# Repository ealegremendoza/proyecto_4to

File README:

Este repositorio contiene gran parte del proyecto de cuarto año a de la carrera de Ingeniería Electrónica de la UTN-FRBA.

Breve descripción de las carptas 
---------------------------------------------------------------------------------------------
En la carpeta "docs" se encuentra toda documentación relacionada al proyecto.
En la carpeta "csv" se encuentran los archivos *.csv para la aplicación.

En la carpeta "code" se encuentra todo código relacionado al proyecto.
En la carpeta "code/dsp" se encuentran las clases para el procesamiento de señales.
En la carpeta "code/gui" se encuentran las clases relacionadas a la interfaz gráfica de la aplicación.

En la carpeta "pcb" se encuentra todos los archivos KiCad relacionados al diseño del PCB.

En la carpeta "lpc_info" se encontrará información útil sobre el microcontrolador utilizado.

NOTAS IMPORTANTES
---------------------------------------------------------------------------------------------

- La interfaz gráfica de este proyecto es realizada en código Python 3.6.5., bajo la plataforma ANACONDA3.
- Hoy en día el código funciona en un SO Ubuntu 16.04 LTS.
- Para correr la aplicación:

	Desde la terminal en el directorio code:
		python3 app.py 

	O desde la terminal en el directorio proyecto_4to:
		python3 code/app.py

	Desde SPYDER:
		Abrir el archivo app.py que se encuentra en el directorio code.
		Presionar F5.
---------------------------------------------------------------------------------------------

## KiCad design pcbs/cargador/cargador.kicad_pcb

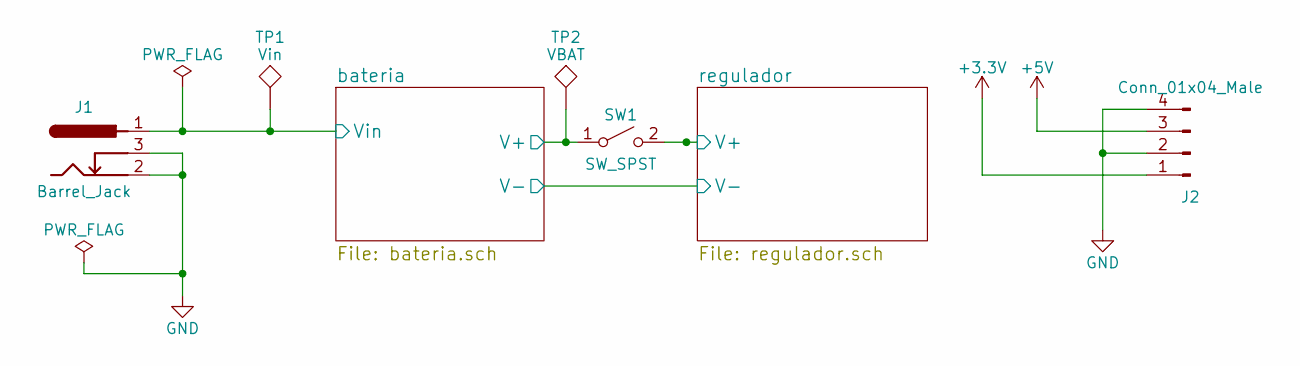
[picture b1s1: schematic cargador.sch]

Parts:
J1: Barrel_Jack; BARREL_JACK
J2: Conn_01x04_Male; Pin_Header_Straight_1x04_Pitch2.54mm
SW1: SW_SPST; Pin_Header_Straight_1x02_Pitch2.54mm
TP1: Vin; TestPoint_Plated_Hole_D2.0mm
TP2: VBAT; TestPoint_Plated_Hole_D2.0mm

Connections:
+3V3: J2.1; also elsewhere on the board
+5V: J2.3; also elsewhere on the board
/bateria/V+: SW1.1 (A), TP2.1; also elsewhere on the board
/regulador/V+: SW1.2 (B); also elsewhere on the board
GND: J1.2, J1.3, J2.2, J2.4; also elsewhere on the board
VCC: J1.1, TP1.1; also elsewhere on the board

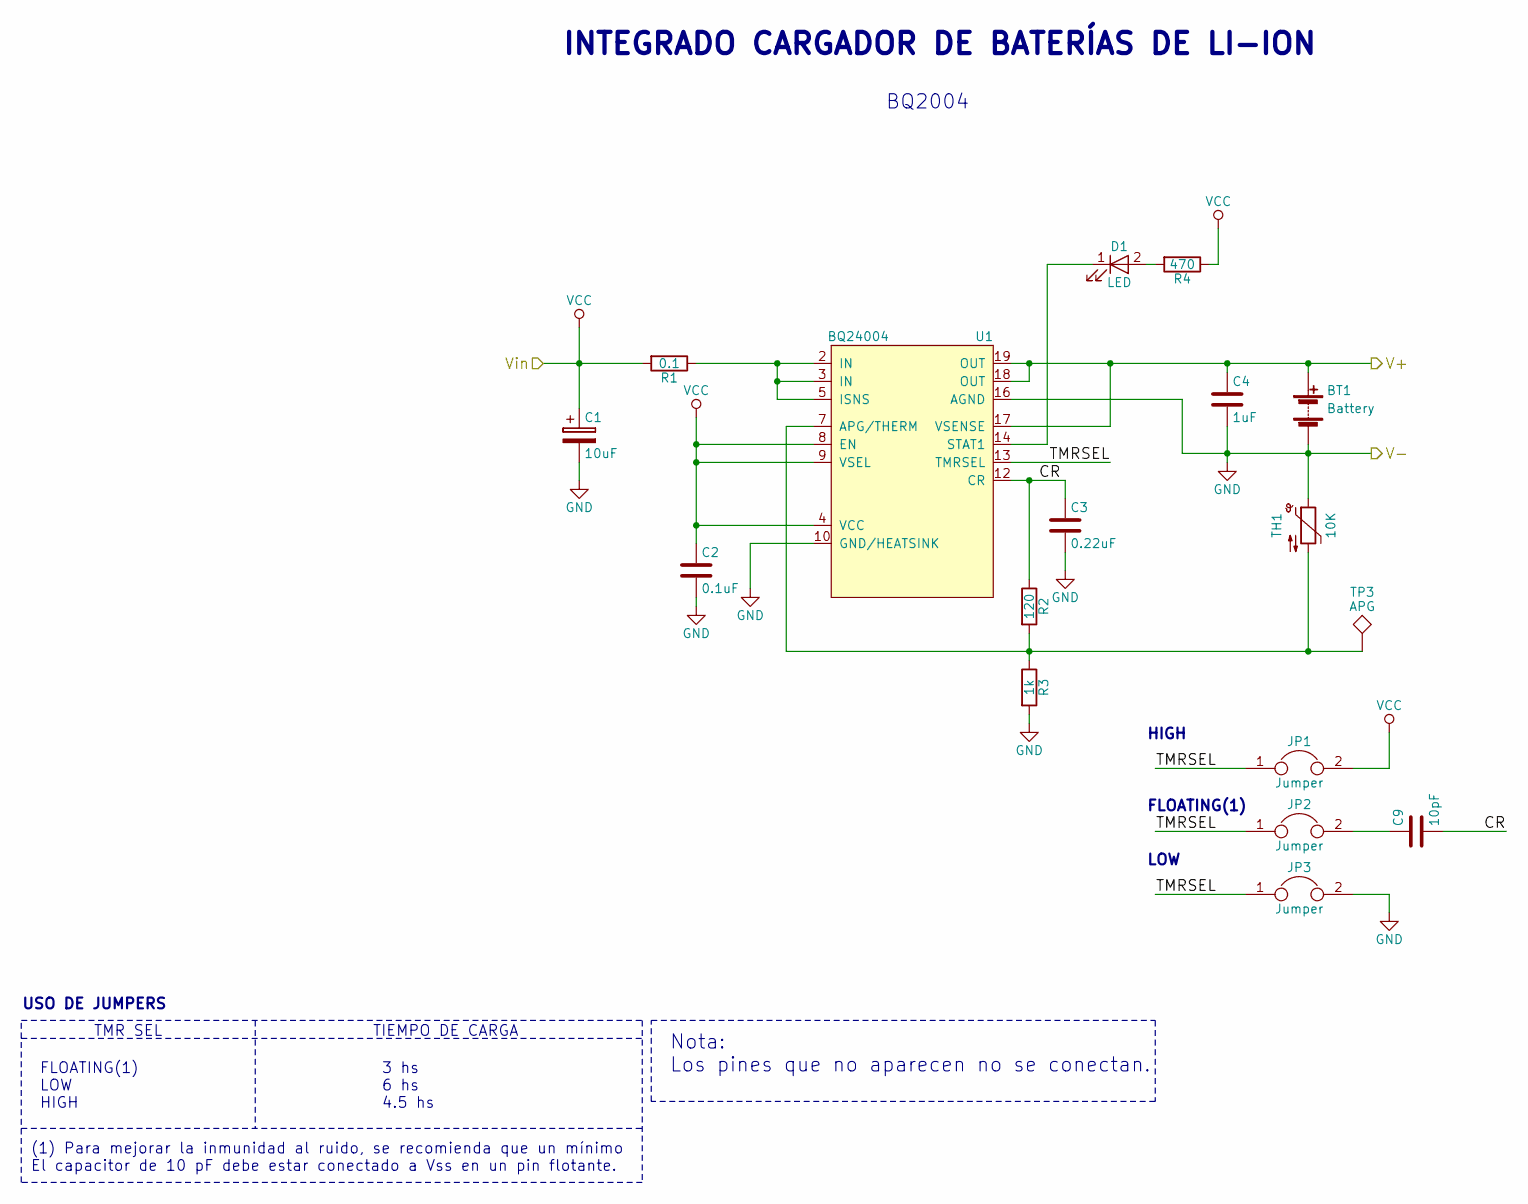
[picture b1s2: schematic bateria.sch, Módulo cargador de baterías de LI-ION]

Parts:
BT1: Battery; TerminalBlock_bornier-2_P5.08mm
C1: 10uF; CP_Tantalum_Case-A_EIA-3216-18_Hand
C2: 0.1uF; C_0805_HandSoldering
C3: 0.22uF; C_0805_HandSoldering
C4: 1uF; C_0805_HandSoldering
C9: 10pF; C_0805_HandSoldering
D1: LED; LED_1206_HandSoldering
JP1, JP2, JP3: Jumper; Pin_Header_Straight_1x02_Pitch2.54mm
R1: 0.1; R_2512_HandSoldering
R2: 120; R_0805_HandSoldering
R3: 1k; R_0805_HandSoldering
R4: 470; R_0805_HandSoldering
TH1: 10K; R_Axial_DIN0207_L6.3mm_D2.5mm_P2.54mm_Vertical
TP3: APG; TestPoint_Plated_Hole_D2.0mm
U1: BQ24004; HTSSOP-20-1EP_4.4x6.5mm_Pitch0.65mm_ThermalPad

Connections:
/bateria/CR: C3.1, C9.2, R2.1, U1.12 (CR)
/bateria/TMRSEL: JP1.1, JP2.1, JP3.1, U1.13 (TMRSEL)
/bateria/V+: BT1.1 (+), C4.1, U1.17 (VSENSE), U1.18 (OUT), U1.19 (OUT); also elsewhere on the board
GND: BT1.2 (-), C1.2, C2.2, C3.2, C4.2, JP3.2, R3.2, TH1.1, U1.10 (GND/HEATSINK), U1.16 (AGND); also elsewhere on the board
unnamed: C9.1, JP2.2
unnamed: D1.1 (K), U1.14 (STAT1)
unnamed: D1.2 (A), R4.2
unnamed: R1.1, U1.2 (IN), U1.3 (IN), U1.5 (ISNS)
unnamed 12: R2.2, R3.1, TH1.2, TP3.1, U1.7 (APG/THERM); also elsewhere on the board
VCC: C1.1, C2.1, JP1.2, R1.2, R4.1, U1.4 (VCC), U1.8 (EN), U1.9 (VSEL); also elsewhere on the board

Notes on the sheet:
INTEGRADO CARGADOR DE BATERÍAS DE LI-ION
BQ2004
Nota: Los pines que no aparecen no se conectan.
FLOATING(1) LOW HIGH
3 hs 6 hs 4.5 hs
TMR SEL
TIEMPO DE CARGA
(1) Para mejorar la inmunidad al ruido, se recomienda que un mínimo El capacitor de 10 pF debe estar conectado a Vss en un pin flotante.
USO DE JUMPERS
HIGH
FLOATING(1)
LOW

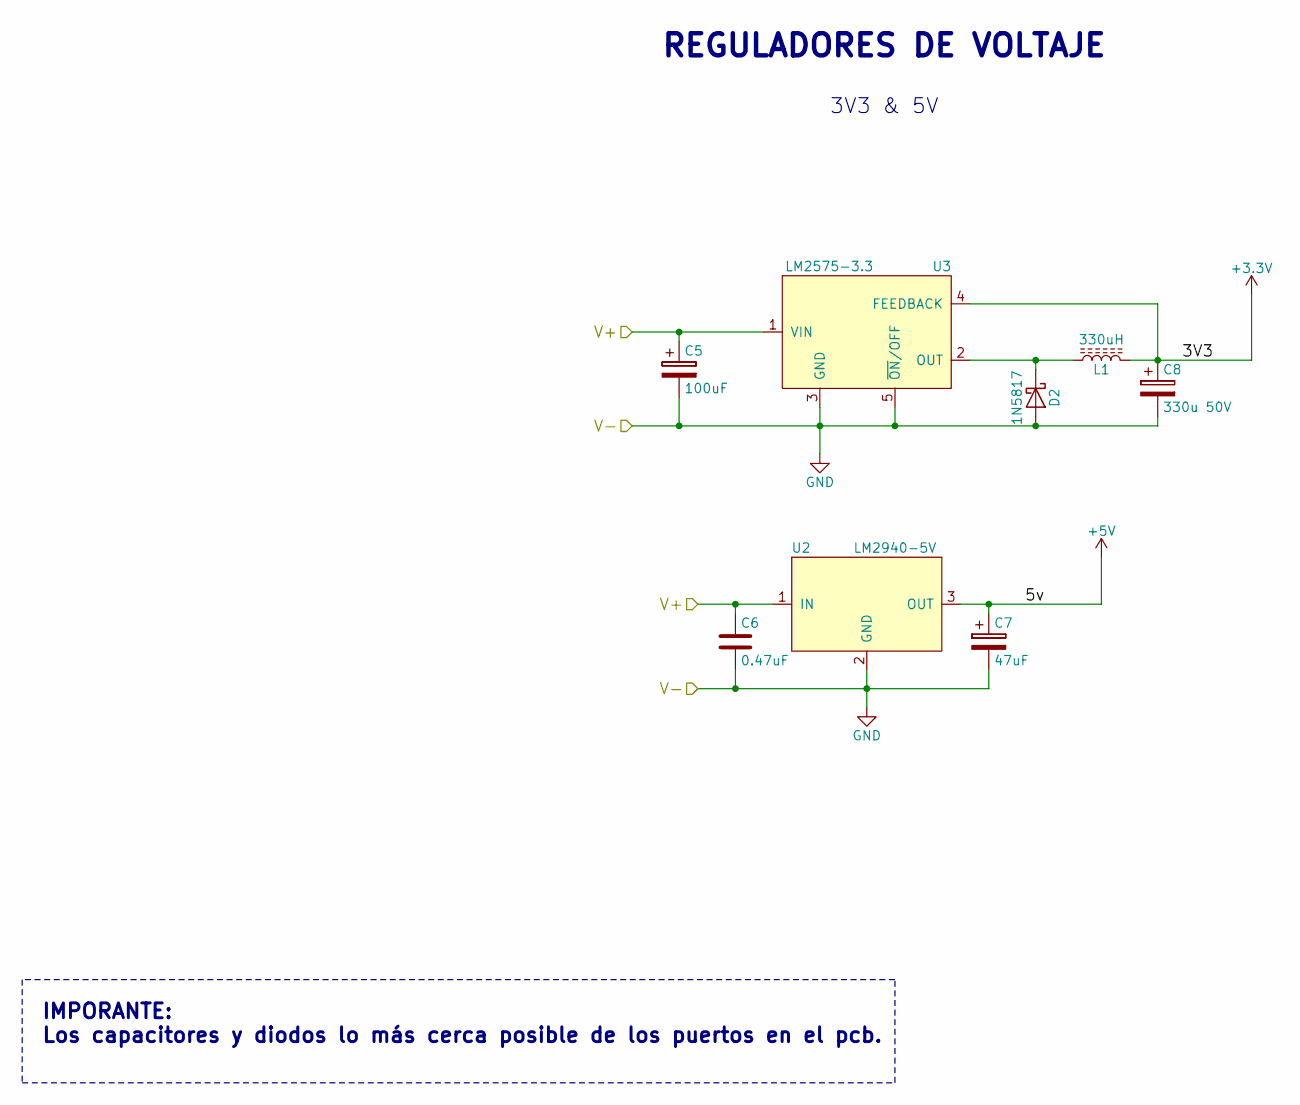
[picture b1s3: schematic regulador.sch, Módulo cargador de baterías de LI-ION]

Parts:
C5: 100uF; CP_Elec_6.3x5.3
C6: 0.47uF; CP_Tantalum_Case-A_EIA-3216-18_Hand
C7: 47uF; CP_Tantalum_Case-C_EIA-6032-28_Hand
C8: 330u 50V; CP_Elec_6.3x7.7
D2: 1N5817; D_DO-41_SOD81_P7.62mm_Horizontal
L1: 330uH; Choke_PK0810
U2: LM2940-5V; SOT-223-3_TabPin2
U3: LM2575-3.3; TO-263-5_TabPin3

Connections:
+3V3: C8.1, L1.2, U3.4 (FEEDBACK); also elsewhere on the board
+5V: C7.1, U2.3 (OUT); also elsewhere on the board
/regulador/V+: C5.1, C6.1, U2.1 (IN), U3.1 (VIN); also elsewhere on the board
GND: C5.2, C6.2, C7.2, C8.2, D2.2 (A), U2.2 (GND), U3.3 (GND), U3.5 (~ON~/OFF); also elsewhere on the board
unnamed: D2.1 (K), L1.1, U3.2 (OUT)

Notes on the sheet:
REGULADORES DE VOLTAJE
3V3 & 5V
IMPORANTE: Los capacitores y diodos lo más cerca posible de los puertos en el pcb.

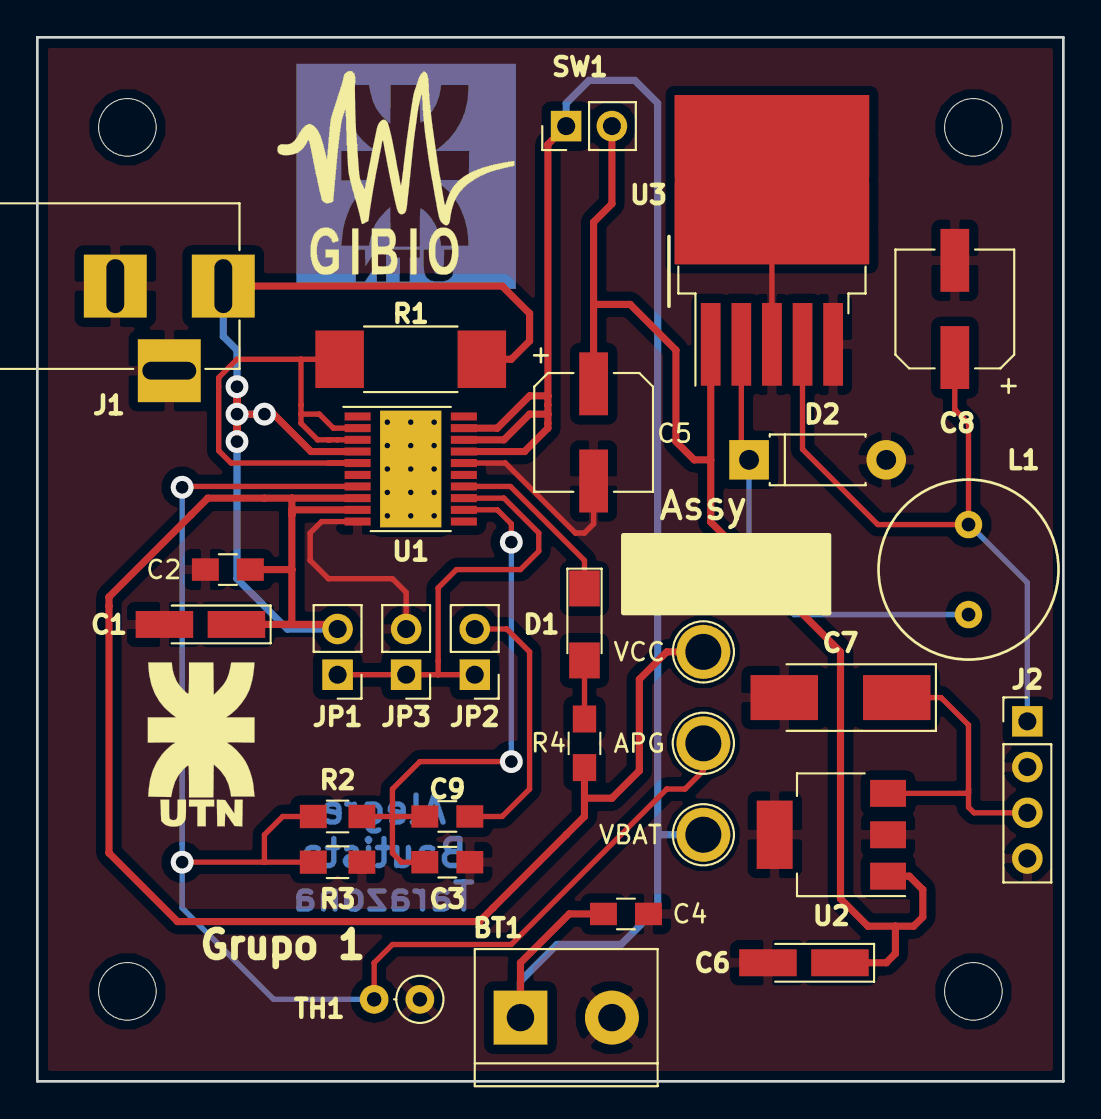
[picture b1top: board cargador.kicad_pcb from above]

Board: 2 copper layers, 57.0 x 58.0 mm, 38 parts (1 on the bottom side), 14 nets.

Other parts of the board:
 : logoUTN1
  : MountingHole_3.2mm_M3_DIN965
  #2: MountingHole_3.2mm_M3_DIN965
 #2,  #3: MountingHole_3.2mm_M3_DIN965
 #4: logoGIBIO
 #5: logoGIBIO5
 #6: logoUTN3
APG: APG; TestPoint_Plated_Hole_D2.0mm
VBAT: VBAT; TestPoint_Plated_Hole_D2.0mm
VCC: Vin; TestPoint_Plated_Hole_D2.0mm

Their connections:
/bateria/V+: VBAT.1; also elsewhere on the board
unnamed 12: APG.1; also elsewhere on the board
VCC: VCC.1; also elsewhere on the board

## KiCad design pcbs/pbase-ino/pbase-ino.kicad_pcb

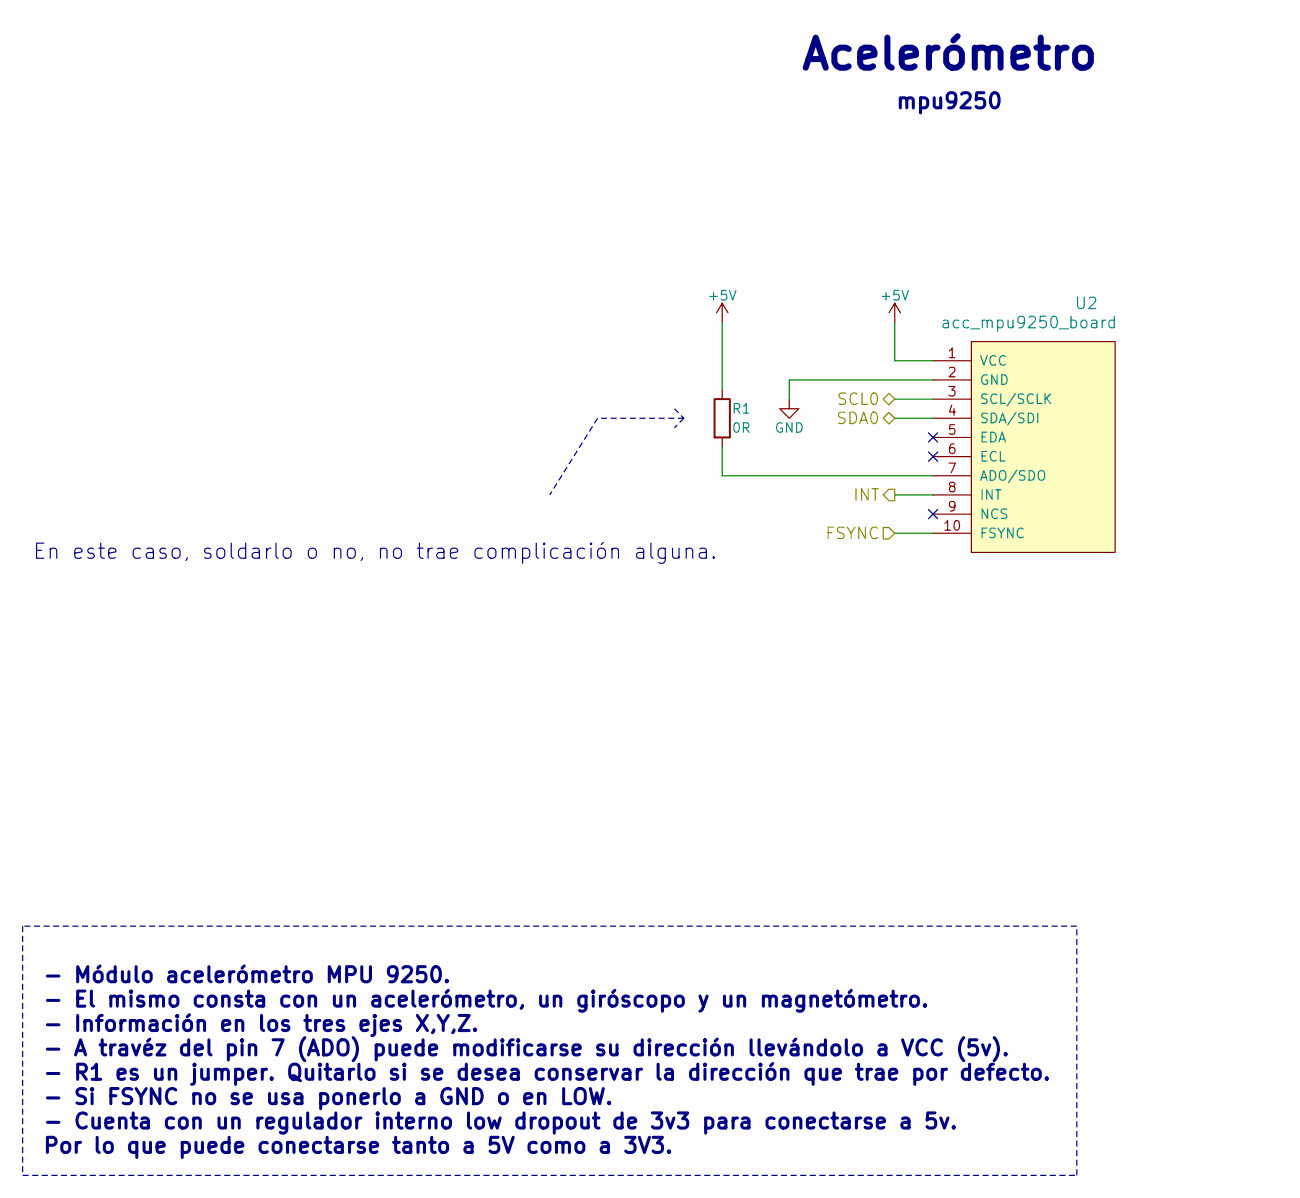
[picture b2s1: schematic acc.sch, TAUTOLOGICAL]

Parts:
R1: 0R; R_0805_HandSoldering
U2: acc_mpu9250_board; mpu9250_board

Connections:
+5V: R1.1, U2.1 (VCC); also elsewhere on the board
/Microcontrolador/FSYNC: U2.10 (FSYNC); also elsewhere on the board
/Microcontrolador/INT: U2.8 (INT); also elsewhere on the board
/Microcontrolador/SCL0: U2.3 (SCL/SCLK); also elsewhere on the board
/Microcontrolador/SDA0: U2.4 (SDA/SDI); also elsewhere on the board
GND: U2.2 (GND); also elsewhere on the board
unnamed: R1.2, U2.7 (ADO/SDO)

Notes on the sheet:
Acelerómetro
- Módulo acelerómetro MPU 9250. - El mismo consta con un acelerómetro, un giróscopo y un magnetómetro. - Información en los tres ejes X,Y,Z. - A travéz del pin 7 (ADO) puede modificarse su dirección llevándolo a VCC (5v). - R1 es un jumper. Quitarlo si se desea conservar la dirección que trae por d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
mpu9250
En este caso, soldarlo o no, no trae complicación alguna.

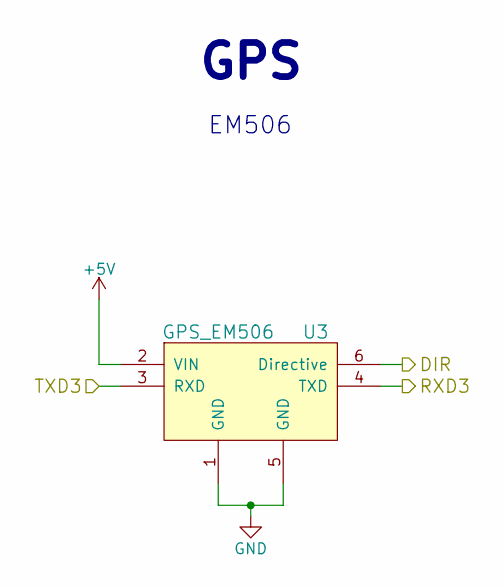
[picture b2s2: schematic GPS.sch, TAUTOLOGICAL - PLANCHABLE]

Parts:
U3: GPS_EM506; JST_SH_SM06B-SRSS-TB_06x1.00mm_Angled

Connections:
+5V: U3.2 (VIN); also elsewhere on the board
/GPS/DIR: U3.6 (Directive); also elsewhere on the board
/GPS/RXD3: U3.4 (TXD); also elsewhere on the board
/GPS/TXD3: U3.3 (RXD); also elsewhere on the board
GND: U3.1 (GND), U3.5 (GND); also elsewhere on the board

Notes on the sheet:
GPS
EM506

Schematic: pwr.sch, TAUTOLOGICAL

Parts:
C3: 100u; CP_Elec_6.3x5.3
C4: 330u; CP_Elec_10x10.5
D1: 1N5817; D_DO-41_SOD81_P7.62mm_Horizontal
J2: Screw_Terminal_01x02; TerminalBlock_bornier-2_P5.08mm
L1: L_Core_Ferrite; Choke_PK0810
SW1: SW_SPST; TerminalBlock_bornier-2_P5.08mm
TP21: VBAT; TestPoint_THTPad_D1.5mm_Drill0.7mm
TP22: 3V3; TestPoint_THTPad_D1.5mm_Drill0.7mm
U1: LM2575-3.3; TO-263-5_TabPin3

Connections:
+3V3: C4.1, D1.1 (K), L1.2, TP22.1, U1.2 (OUT); also elsewhere on the board
/Alimentación/VBat: C3.1, SW1.2, TP21.1, U1.1 (VIN); also elsewhere on the board
GND: C3.2, C4.2, D1.2 (A), J2.1, U1.3 (GND), U1.5 (~ON~/OFF); also elsewhere on the board
unnamed: J2.2, SW1.1
unnamed: L1.1, U1.4 (FEEDBACK)

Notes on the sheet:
Alimentación
IMPORTANTE: C3, D1 y C4 lo mas cerca posible del puerto y GND.
Fuente Switching 3v3
3V3: - Tarjeta SD - Comunicación Inalámbrica Zigbee. VBAT: - Arduino MEGA 5v: - GPS. EM506. - Acelerómetro. MPU9250.

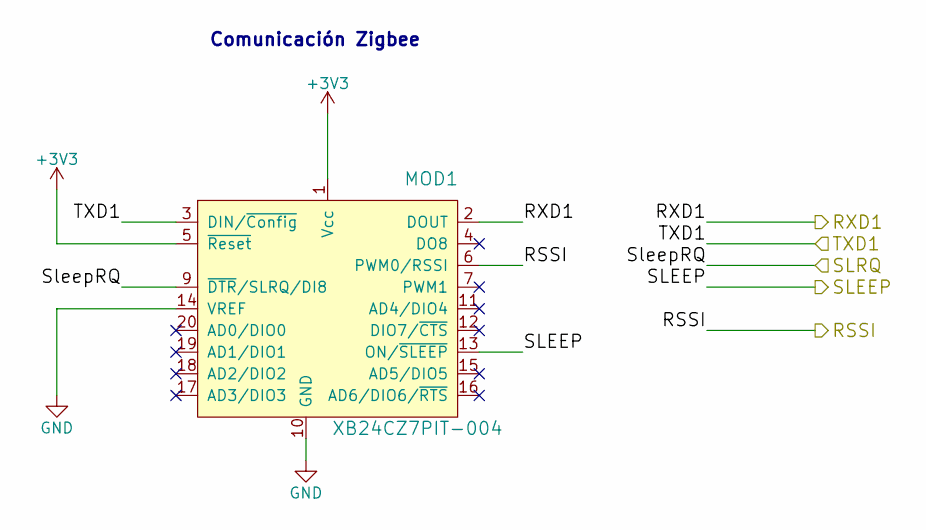
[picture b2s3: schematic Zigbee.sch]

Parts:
MOD1: XB24CZ7PIT-004; xbee_xb24cz7pit_004; MPN XB24CZ7PIT-004; Digi-Key_PN 602-1557-ND

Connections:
+3V3: MOD1.1 (Vcc), MOD1.5 (~Reset); also elsewhere on the board
/Microcontrolador/CAP2.1: MOD1.6 (PWM0/RSSI); also elsewhere on the board
/Microcontrolador/RXD1: MOD1.2 (DOUT); also elsewhere on the board
/Microcontrolador/SLEEP: MOD1.13 (ON/~SLEEP); also elsewhere on the board
/Microcontrolador/TXD1: MOD1.3 (DIN/~Config); also elsewhere on the board
/Zigbee/SLRQ: MOD1.9 (~DTR~/SLRQ/DI8); also elsewhere on the board
GND: MOD1.10 (GND), MOD1.14 (VREF); also elsewhere on the board

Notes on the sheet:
Comunicación Zigbee

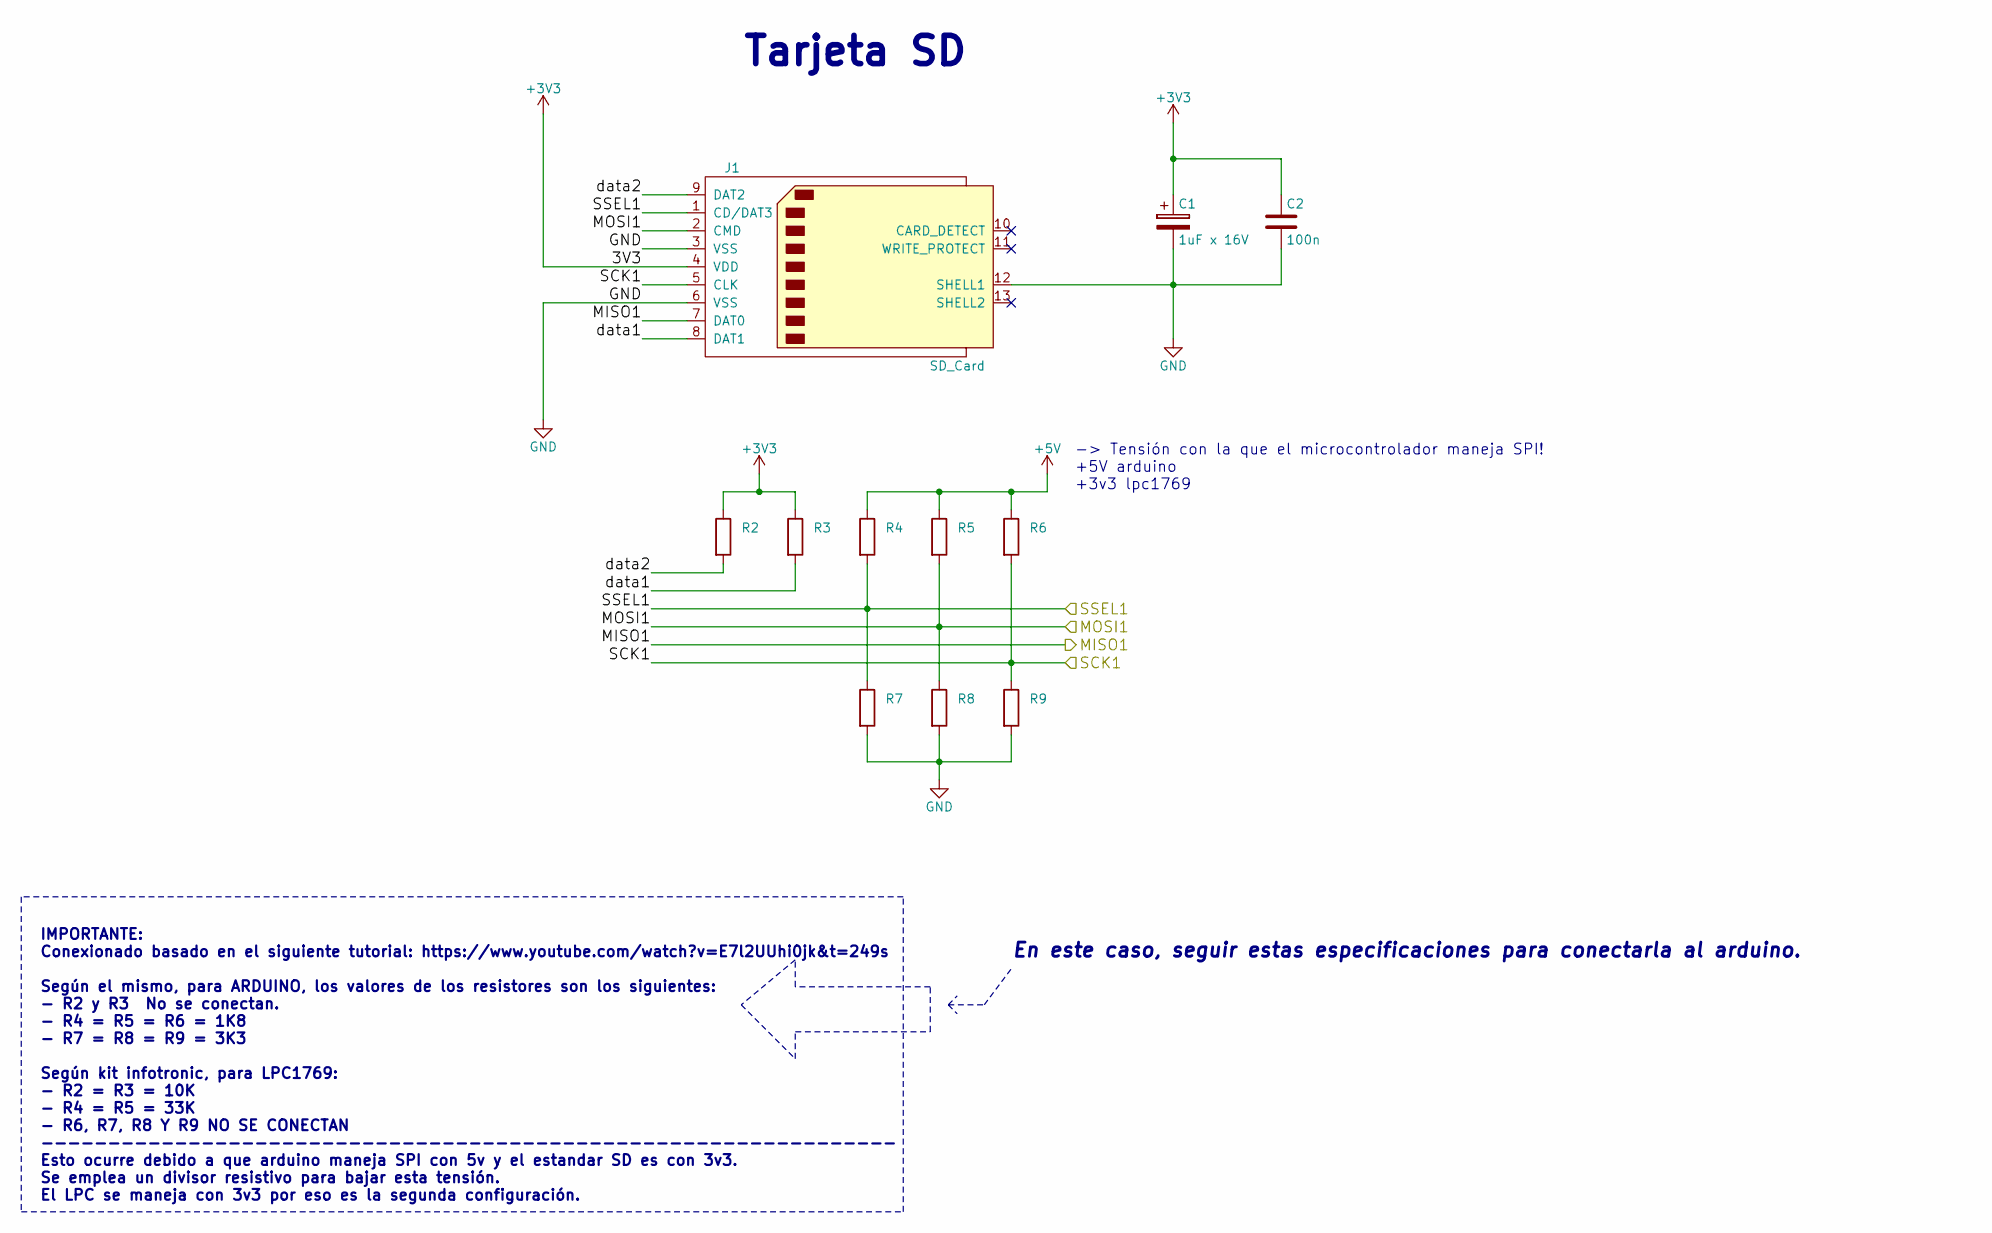
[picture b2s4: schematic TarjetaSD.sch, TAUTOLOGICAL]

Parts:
C1: 1uF x 16V; CP_Tantalum_Case-A_EIA-3216-18_Hand
C2: 100n; C_0805_HandSoldering
J1: SD_Card; SD_TE_2041021_edit
R2, R3: 10K; R_0805_HandSoldering
R4: r4; R_0805_HandSoldering
R5: r5; R_0805_HandSoldering
R6: r6; R_0805_HandSoldering
R7: r7; R_0805_HandSoldering
R8: r8; R_0805_HandSoldering
R9: r9; R_0805_HandSoldering

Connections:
+3V3: C1.1, C2.1, J1.4 (VDD), R2.1, R3.1; also elsewhere on the board
+5V: R4.1, R5.1, R6.1; also elsewhere on the board
/Microcontrolador/MISO1: J1.7 (DAT0); also elsewhere on the board
/Microcontrolador/MOSI1: J1.2 (CMD), R5.2, R8.1; also elsewhere on the board
/Microcontrolador/SCK1: J1.5 (CLK), R6.2, R9.1; also elsewhere on the board
/Microcontrolador/SSEL1: J1.1 (CD/DAT3), R4.2, R7.1; also elsewhere on the board
/Tarjeta SD/data1: J1.8 (DAT1), R3.2
/Tarjeta SD/data2: J1.9 (DAT2), R2.2
GND: C1.2, C2.2, J1.3 (VSS), J1.6 (VSS), J1.12 (SHELL1), R7.2, R8.2, R9.2; also elsewhere on the board

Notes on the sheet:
Tarjeta SD
IMPORTANTE: Conexionado basado en el siguiente tutorial: https://www.youtube.com/watch?v=E7l2UUhi0jk&t=249s Según el mismo, para ARDUINO, los valores de los resistores son los siguientes: - R2 y R3 No se conectan. - R4 = R5 = R6 = 1K8 - R7 = R8 = R9 = 3K3 Según kit infotronic, para LPC1769: - R2 = 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
-> Tensión con la que el microcontrolador maneja SPI! +5V arduino +3v3 lpc1769
En este caso, seguir estas especificaciones para conectarla al arduino.

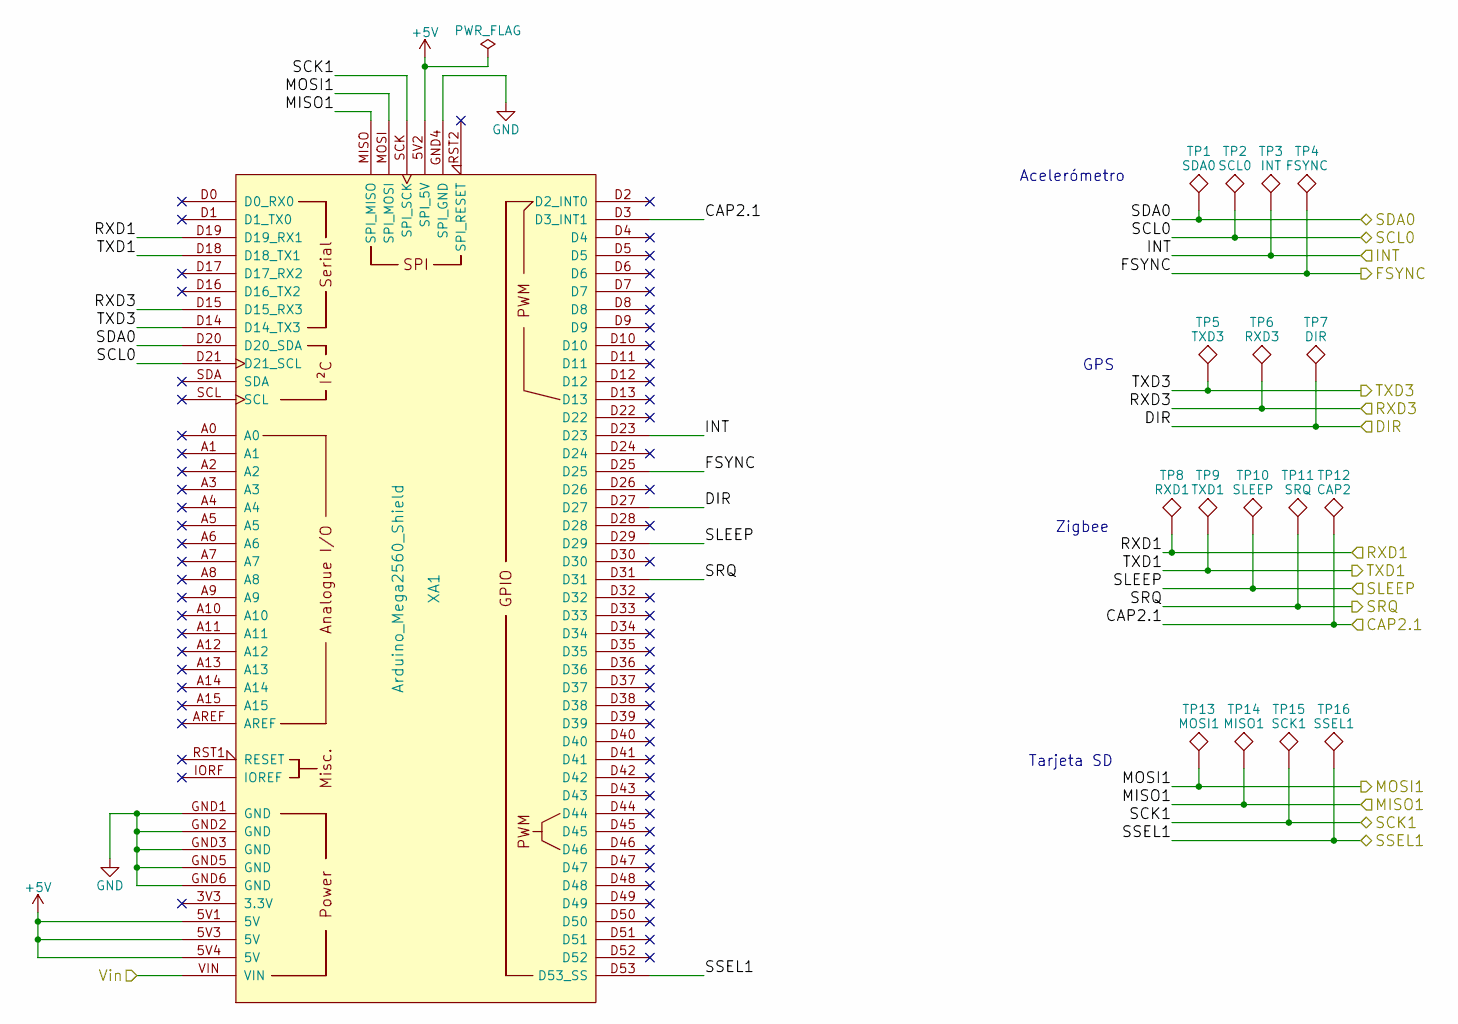
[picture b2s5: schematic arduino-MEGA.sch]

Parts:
TP1: SDA0; TestPoint_THTPad_D1.5mm_Drill0.7mm
TP2: SCL0; TestPoint_THTPad_D1.5mm_Drill0.7mm
TP3: INT; TestPoint_THTPad_D1.5mm_Drill0.7mm
TP4: FSYNC; TestPoint_THTPad_D1.5mm_Drill0.7mm
TP5: TXD3; TestPoint_THTPad_D1.5mm_Drill0.7mm
TP6: RXD3; TestPoint_THTPad_D1.5mm_Drill0.7mm
TP7: DIR; TestPoint_THTPad_D1.5mm_Drill0.7mm
TP8: RXD1; TestPoint_THTPad_D1.5mm_Drill0.7mm
TP9: TXD1; TestPoint_THTPad_D1.5mm_Drill0.7mm
TP10: SLEEP; TestPoint_THTPad_D1.5mm_Drill0.7mm
TP11: SRQ; TestPoint_THTPad_D1.5mm_Drill0.7mm
TP12: CAP2; TestPoint_THTPad_D1.5mm_Drill0.7mm
TP13: MOSI1; TestPoint_THTPad_D1.5mm_Drill0.7mm
TP14: MISO1; TestPoint_THTPad_D1.5mm_Drill0.7mm
TP15: SCK1; TestPoint_THTPad_D1.5mm_Drill0.7mm
TP16: SSEL1; TestPoint_THTPad_D1.5mm_Drill0.7mm
XA1: Arduino_Mega2560_Shield; Arduino_Mega2560_Shield_flippedONtop

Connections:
+5V: XA1.5V1 (5V), XA1.5V2 (SPI_5V), XA1.5V3 (5V), XA1.5V4 (5V); also elsewhere on the board
/Alimentación/VBat: XA1.VIN; also elsewhere on the board
/GPS/DIR: TP7.1, XA1.D27; also elsewhere on the board
/GPS/RXD3: TP6.1, XA1.D15 (D15_RX3); also elsewhere on the board
/GPS/TXD3: TP5.1, XA1.D14 (D14_TX3); also elsewhere on the board
/Microcontrolador/CAP2.1: TP12.1, XA1.D3 (D3_INT1); also elsewhere on the board
/Microcontrolador/FSYNC: TP4.1, XA1.D25; also elsewhere on the board
/Microcontrolador/INT: TP3.1, XA1.D23; also elsewhere on the board
/Microcontrolador/MISO1: TP14.1, XA1.MISO (SPI_MISO); also elsewhere on the board
/Microcontrolador/MOSI1: TP13.1, XA1.MOSI (SPI_MOSI); also elsewhere on the board
/Microcontrolador/RXD1: TP8.1, XA1.D19 (D19_RX1); also elsewhere on the board
/Microcontrolador/SCK1: TP15.1, XA1.SCK (SPI_SCK); also elsewhere on the board
/Microcontrolador/SCL0: TP2.1, XA1.D21 (D21_SCL); also elsewhere on the board
/Microcontrolador/SDA0: TP1.1, XA1.D20 (D20_SDA); also elsewhere on the board
/Microcontrolador/SLEEP: TP10.1, XA1.D29; also elsewhere on the board
/Microcontrolador/SSEL1: TP16.1, XA1.D53 (D53_SS); also elsewhere on the board
/Microcontrolador/TXD1: TP9.1, XA1.D18 (D18_TX1); also elsewhere on the board
/Zigbee/SLRQ: TP11.1, XA1.D31; also elsewhere on the board
GND: XA1.GND1 (GND), XA1.GND2 (GND), XA1.GND3 (GND), XA1.GND4 (SPI_GND), XA1.GND5 (GND), XA1.GND6 (GND); also elsewhere on the board

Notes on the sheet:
Acelerómetro
GPS
Zigbee
Tarjeta SD

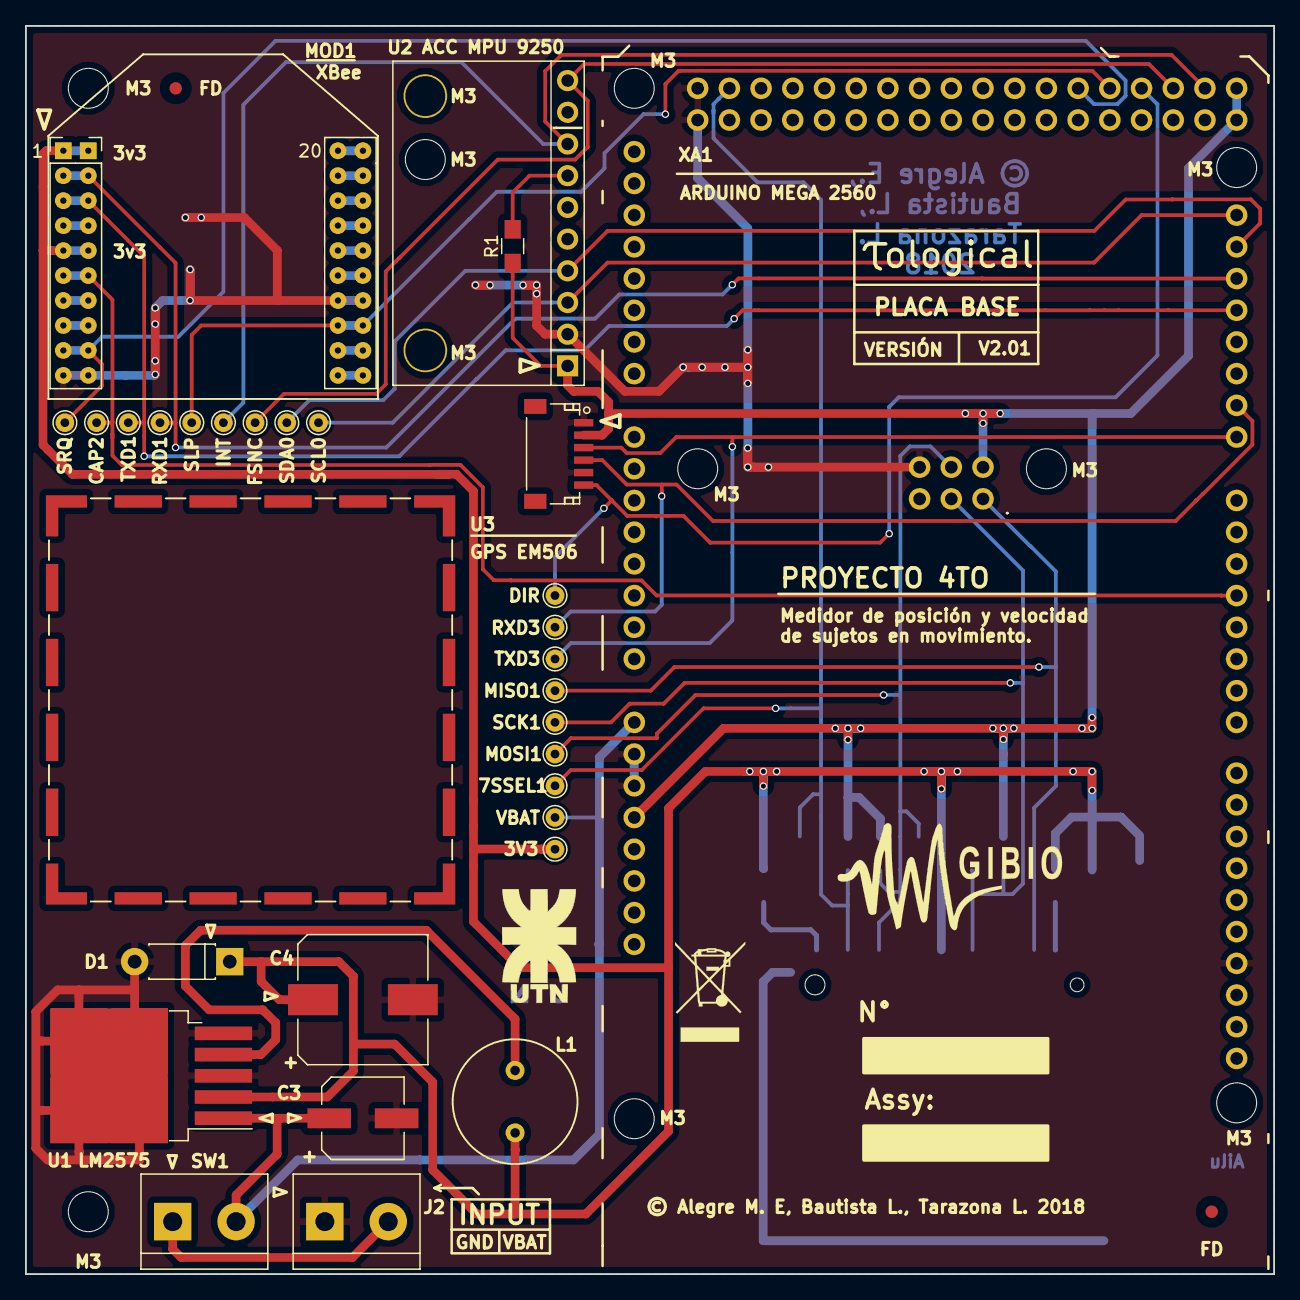
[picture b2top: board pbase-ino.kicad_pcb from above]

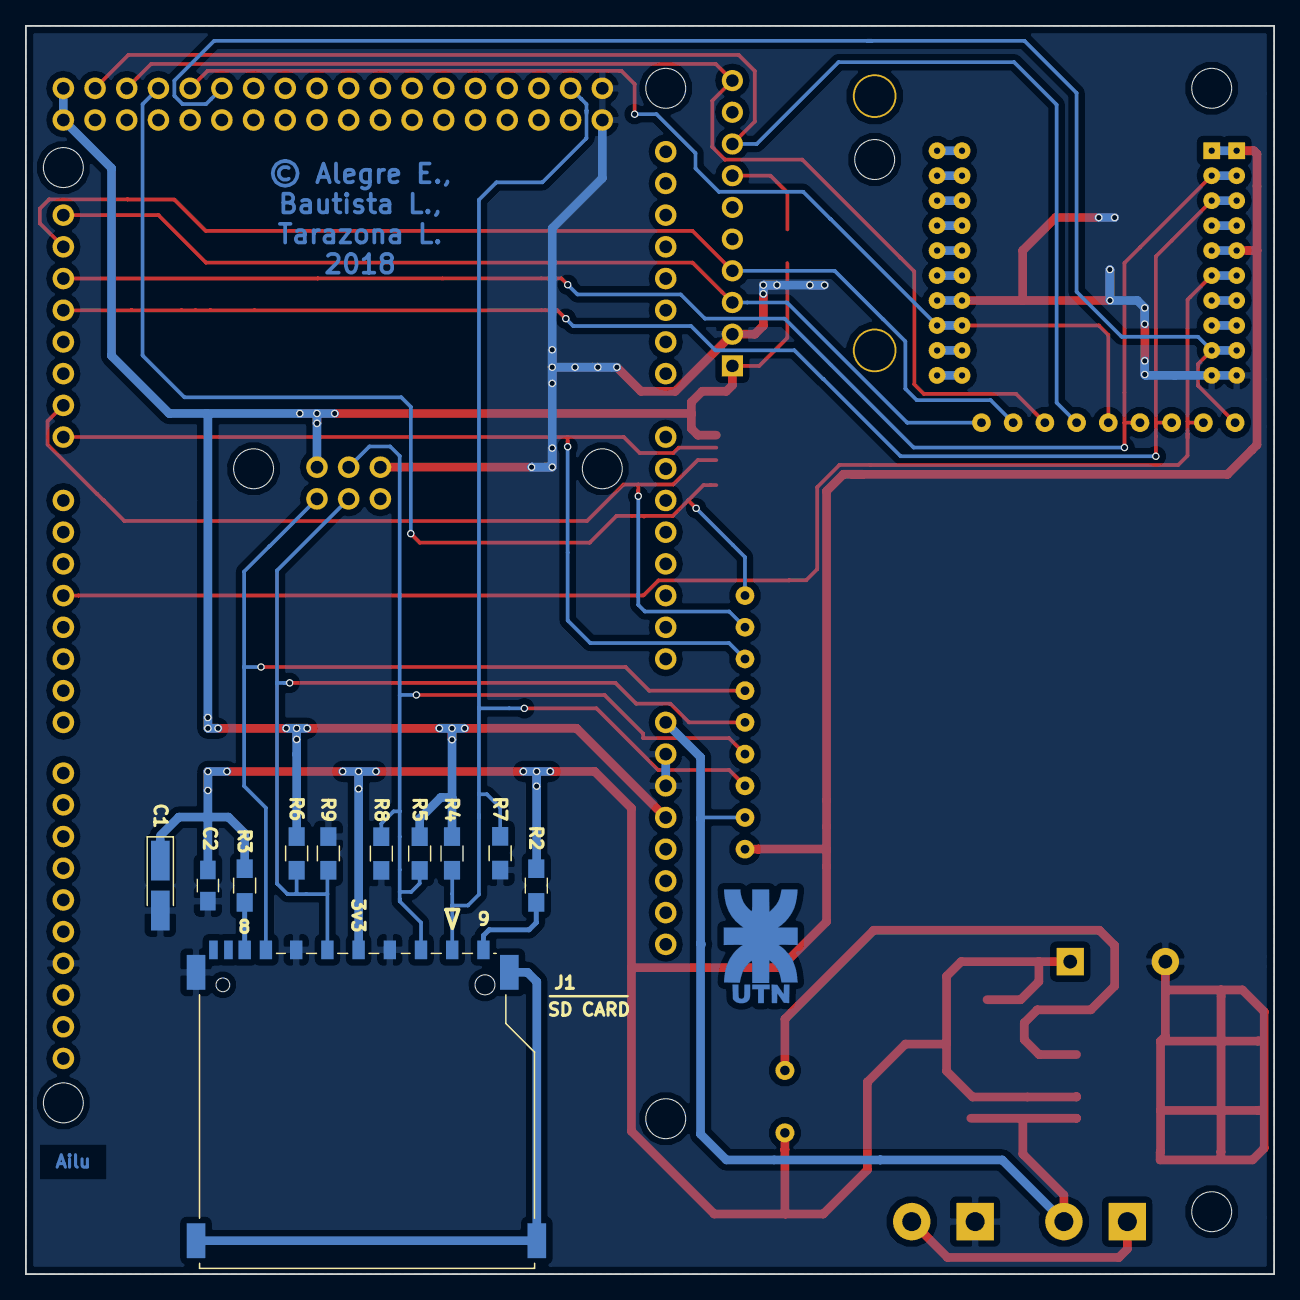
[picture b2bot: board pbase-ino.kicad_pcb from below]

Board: 2 copper layers, 100.0 x 100.0 mm, 47 parts (12 on the bottom side), 25 nets.

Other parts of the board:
FD: Fiducial_1mm_Dia_2.54mm_Outer_CopperTop
FD#2: Fiducial_1mm_Dia_2.54mm_Outer_CopperTop
GPS EM506: Laird_Technologies_BMI-S-204-F_32.00x32.00mm
M3, M3#2, M3#3: MountingHole_3.2mm_M3_DIN965

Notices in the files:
pcbs/pbase-ino/pbase-ino.kicad_pcb:
© Alegre E.,
Bautista L.,
© Alegre M. E, Bautista L., Tarazona L. 2018
pcbs/pbase/pbase.kicad_pcb:
© Alegre M.E.,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
